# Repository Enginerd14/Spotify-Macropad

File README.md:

# Spotify-Macropad
## What is it and why I made it
### A small keyboard called a macropad designed to control songs on spotify and media on YouTube.

## Hackpad
###  

## Schematic 
### 

## PCB
### 

## BOM
- 4x Cherry MX Switches
- 1x XIAO RP2040
- 1x EC11 Rotary Encoder
- 1x SSD11306 0.91" OLED Display
- 4x Blank DSA Keycaps
- 4x M3x16 Bolt
- 4x M3 Heatset

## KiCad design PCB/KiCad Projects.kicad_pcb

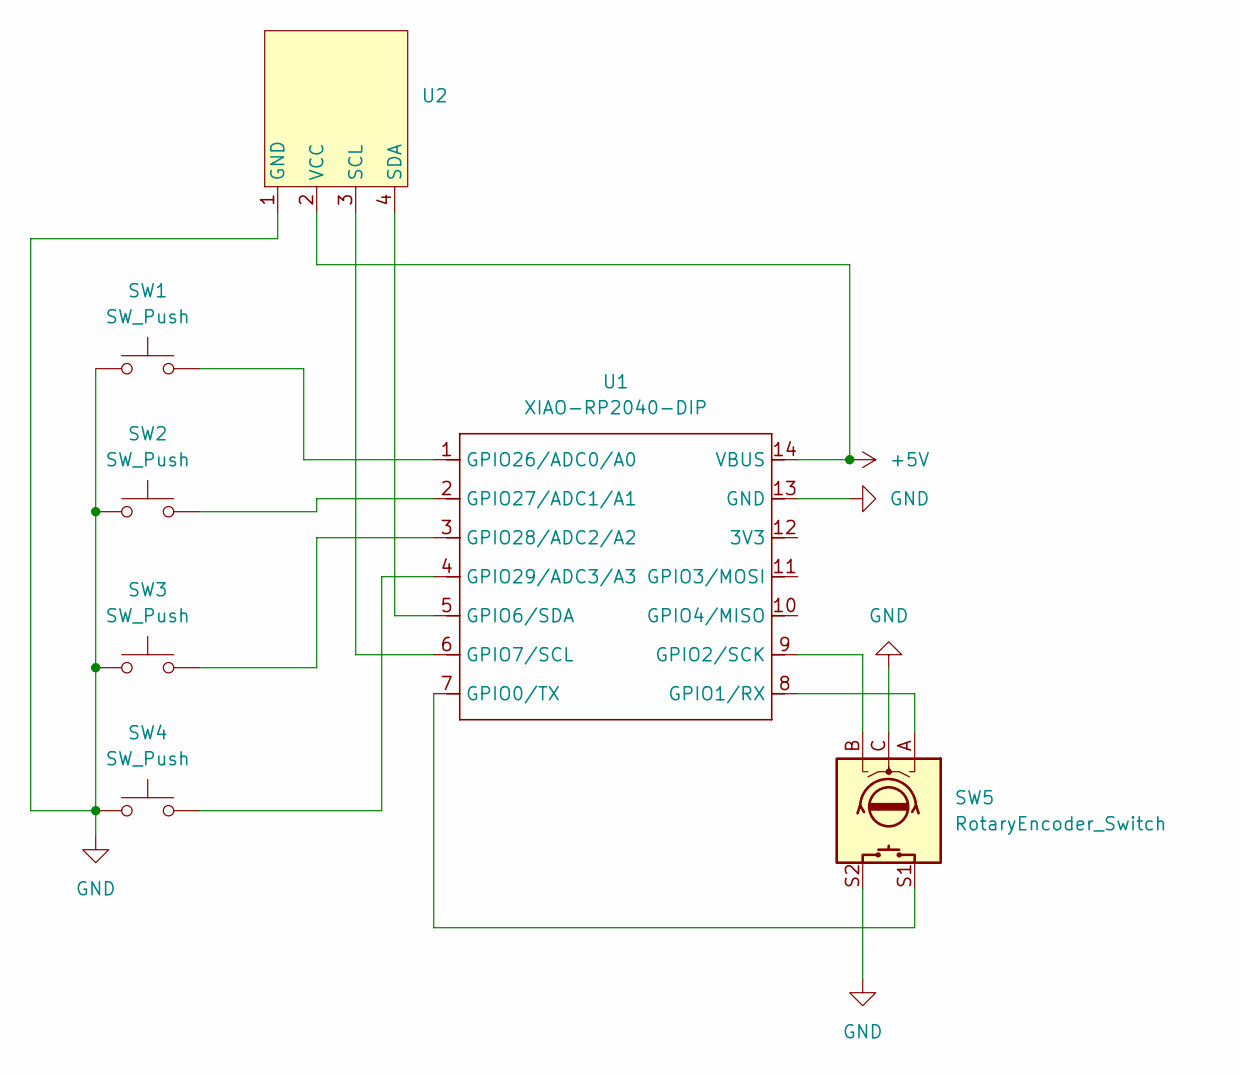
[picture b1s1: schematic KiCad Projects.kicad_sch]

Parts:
SW1, SW2, SW3, SW4: SW_Push; SW_Cherry_MX_1.00u_PCB
SW5: RotaryEncoder_Switch; RotaryEncoder_Alps_EC11E-Switch_Vertical_H20mm
U1: XIAO-RP2040-DIP
U2: SSD1306-0.91-OLED-4pin-128x32

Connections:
+5V: U1.14 (VBUS), U2.2 (VCC)
GND: SW1.1, SW2.1, SW3.1, SW4.1, SW5.C, SW5.S2, U1.13 (GND), U2.1 (GND)
unnamed: SW5.S1, U1.7 (GPIO0/TX)
unnamed: SW5.A, U1.8 (GPIO1/RX)
unnamed: SW5.B, U1.9 (GPIO2/SCK)
unnamed: U1.5 (GPIO6/SDA), U2.4 (SDA)
unnamed: U1.6 (GPIO7/SCL), U2.3 (SCL)
unnamed: SW1.2, U1.1 (GPIO26/ADC0/A0)
unnamed: SW2.2, U1.2 (GPIO27/ADC1/A1)
unnamed: SW3.2, U1.3 (GPIO28/ADC2/A2)
unnamed: SW4.2, U1.4 (GPIO29/ADC3/A3)

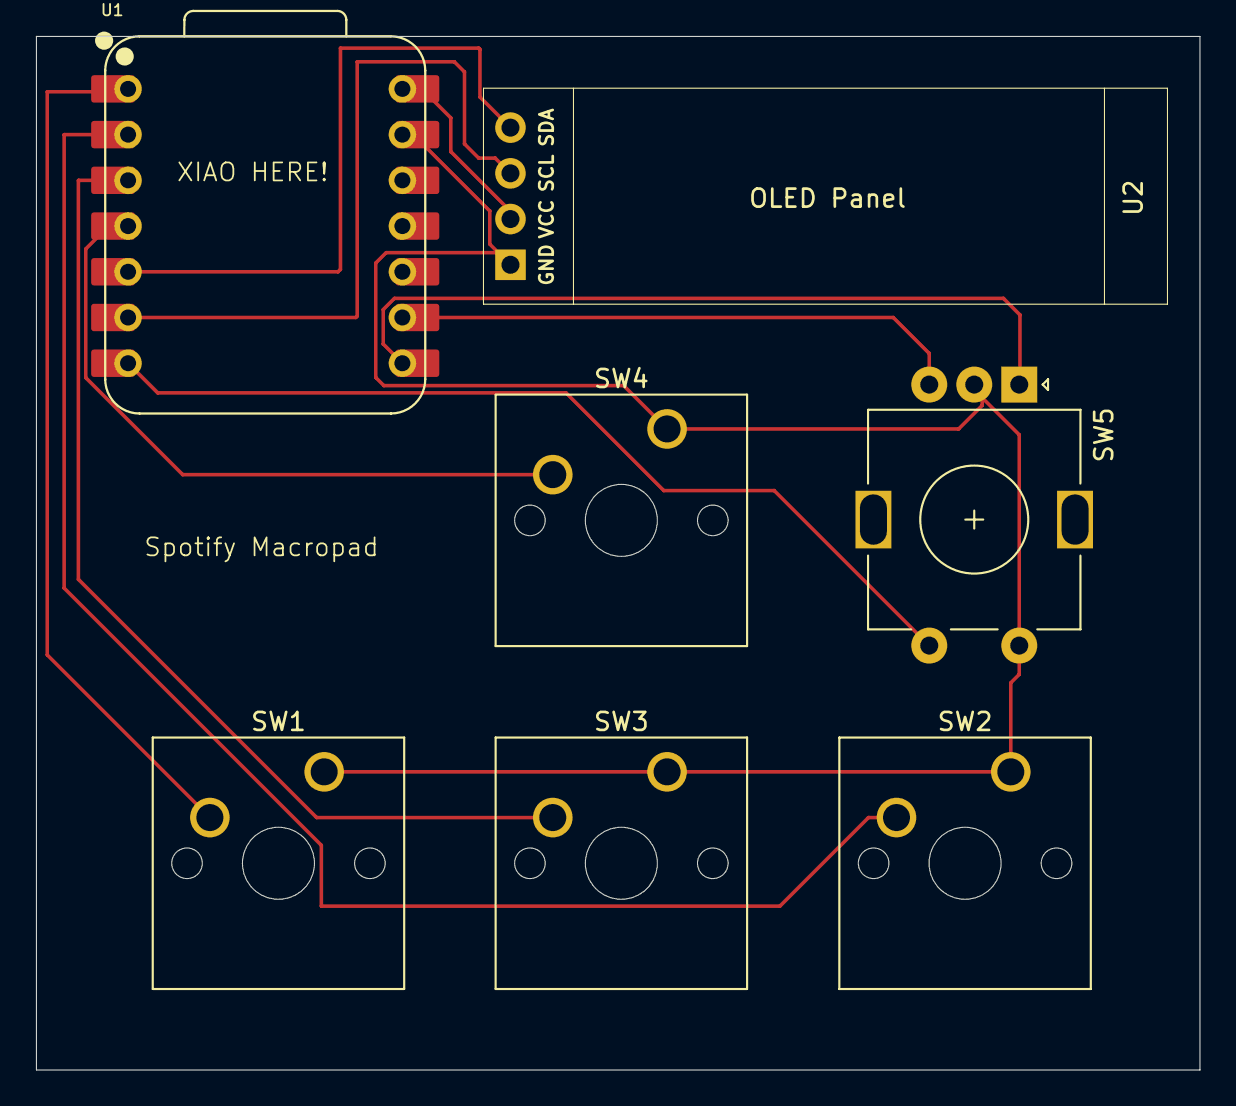
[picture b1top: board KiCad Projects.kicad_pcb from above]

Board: 2 copper layers, 64.6 x 57.4 mm, 7 parts (0 on the bottom side), 11 nets.

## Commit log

2025-12-07 Create Macropad Assembled
2025-12-07 Create KiCad
2026-03-14 Fix image formatting in README.md
2026-03-14 Add header to README for Hackpad section
2026-03-14 Create cad
2026-03-14 Add project description to README
